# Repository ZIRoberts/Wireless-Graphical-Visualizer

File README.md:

# Wireless-Graphical-Visualizer
Maintain all documents relating to the creation of the Realtime Wireless Graphical Equalizer.  All symbols, schematics, footprints, and board layouts are designed in KiCad.

# Overview

There is a single board in this sytem and it is broken up into three sections represented by their own respeitive schematic sheet. The first section is the board's inputs. This includes the audio input, power input and regulation, and the audio isolation buffer. Audio is input by a standard 3.5 mm audio cable through one of the two linked audio jacks and enters the system by passing through the unity gain isolation buffer. The two audio jacks are to allow for the user to pass the audio through the device to a speaker without any disortion caused by the filters. Power is inputed by a standard USB Type-B mini cable. There are two 2.5 V linear regulators connected directly to the input line. One serves as a virtual ground to refence the audio signal two later in on in the single supply band pass filters. The other is used on the output of the filters as a voltage calmp to ensure the microcontroller will not get damaged due to an unexpectedly large singal being passed through the filters.

The second section is the bandpass filter section. There are 8 multiple feedback band pass filters. Multifple feed back band pass fitlers were selected based on their low componet cost, moderate gain, and able to handle to filter a signal up to around 5 Q. The 8 bands are tuned to the fallowing frequnecies: 160, 250, 400, 800, 1000, 2500, 4000, and 6500 Hz. The frequncies are filted through their specified filter, have their DC offset stripped, pass through a half-wave rectifer and a 22 uF capacitor to keep the signal from instantly dissapating. This output is then passed through a voltage clamp consiting of a 2.5 V linear regulator and a 500 mV foward voltage diode to prevent the output signal from passive above 3 V as any input above 3V3 would fry the microcontroller. 

The third section is the microcontoller and multiplexor. This section cotnains the connections for the selected ESP32 microcontroller along with the mux. The mux is used to select which of the 8 filtered outputs would be read in by the microcontroller. The MCU used for this project is the ESP32 by Espressiff Systems. This microcontroller was sekected because it was of appropriate size, had appropriate pin count, built in wireless communication, compatablity with Arduino libraries, and the creator already had experience using this family of microcontrollers. This sheet also holds the diodes used for the voltage clamp discribed on in the previous section.

A full list of electronic components can be found in the Bill of Materials.xlsx and images of the design can be found below.

# Schematic
## Aduio and Power Sheet

## Bandpass Filter Sheet

## Microcontroller sheet

# PCB Layout
## Front Copper 

## Back Copper

# 3D Renders
## Front Render

## Bottom Render

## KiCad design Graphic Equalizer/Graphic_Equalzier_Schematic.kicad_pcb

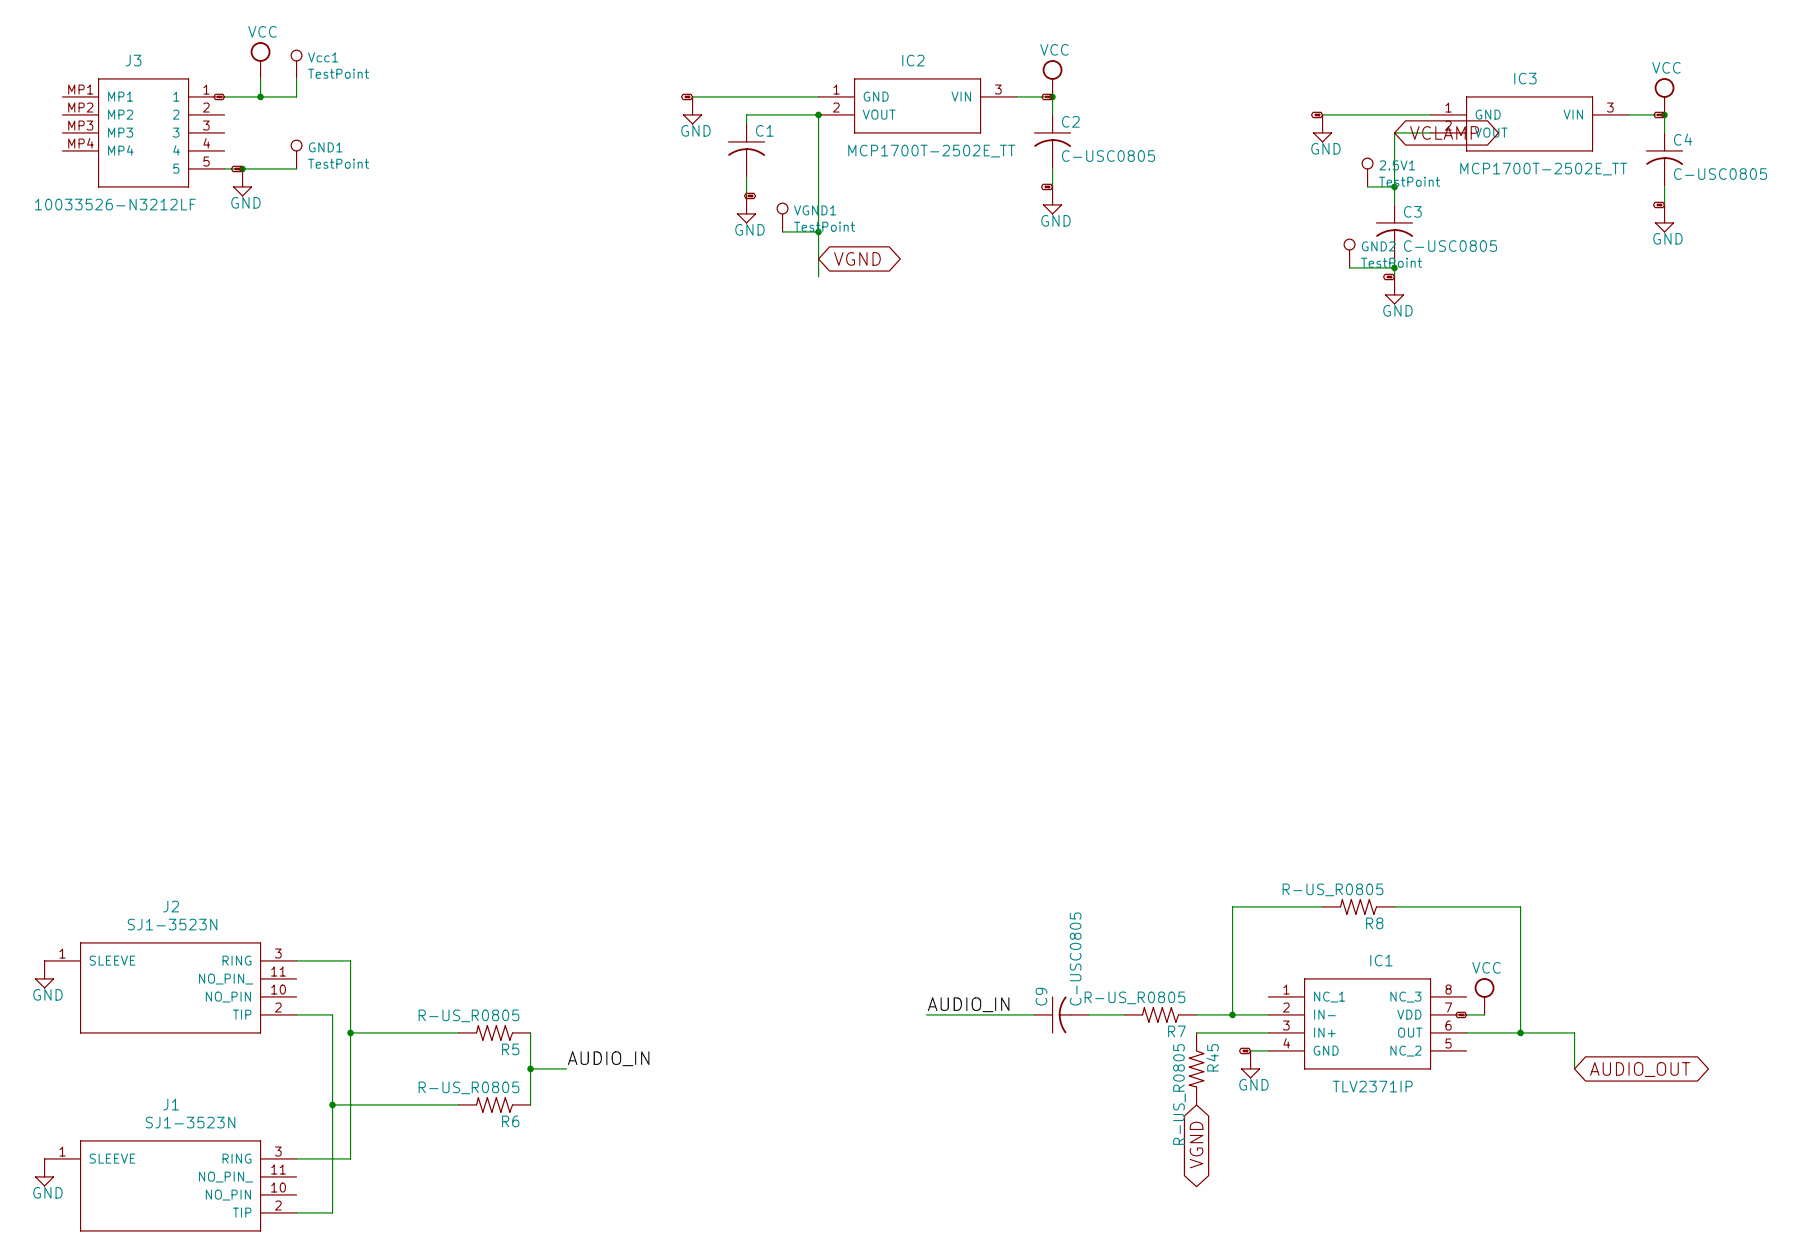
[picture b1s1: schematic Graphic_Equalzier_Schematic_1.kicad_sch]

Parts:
2.5V1: TestPoint; TestPoint_THTPad_D2.0mm_Drill1.0mm
C1, C2, C3, C4, C9: C-USC0805; C0805
GND1, GND2: TestPoint; TestPoint_THTPad_D2.0mm_Drill1.0mm
IC1: TLV2371IP; DIP794W53P254L959H508Q8N
IC2, IC3: MCP1700T-2502E_TT; SOT95P237X112-3N
J1, J2: SJ1-3523N; SJ13523N
J3: 10033526-N3212LF; 10033526N3212LF
R5, R6, R7, R8, R45: R-US_R0805; R0805
VGND1: TestPoint; TestPoint_THTPad_D2.0mm_Drill1.0mm
Vcc1: TestPoint; TestPoint_THTPad_D2.0mm_Drill1.0mm

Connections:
/Graphic_Equalzier_Schematic_1/AUDIO_IN: C9.1, R5.1, R6.1
AUDIO_OUT: IC1.6 (OUT), R8.1; also elsewhere on the board
GND: C1.2, C2.2, C3.2, C4.2, GND1.1, GND2.1, IC1.4 (GND), IC2.1 (GND), IC3.1 (GND), J1.1 (SLEEVE), J2.1 (SLEEVE), J3.5; also elsewhere on the board
unnamed: C9.2, R7.2
unnamed: IC1.2 (IN-), R7.1, R8.2
unnamed: IC1.3 (IN+), R45.1
unnamed: J1.2 (TIP), J2.2 (TIP), R6.2
unnamed: J1.3 (RING), J2.3 (RING), R5.2
VCC: C2.1, C4.1, IC1.7 (VDD), IC2.3 (VIN), IC3.3 (VIN), J3.1, Vcc1.1; also elsewhere on the board
VCLAMP: 2.5V1.1, C3.1, IC3.2 (VOUT); also elsewhere on the board
VGND: C1.1, IC2.2 (VOUT), R45.2, VGND1.1; also elsewhere on the board

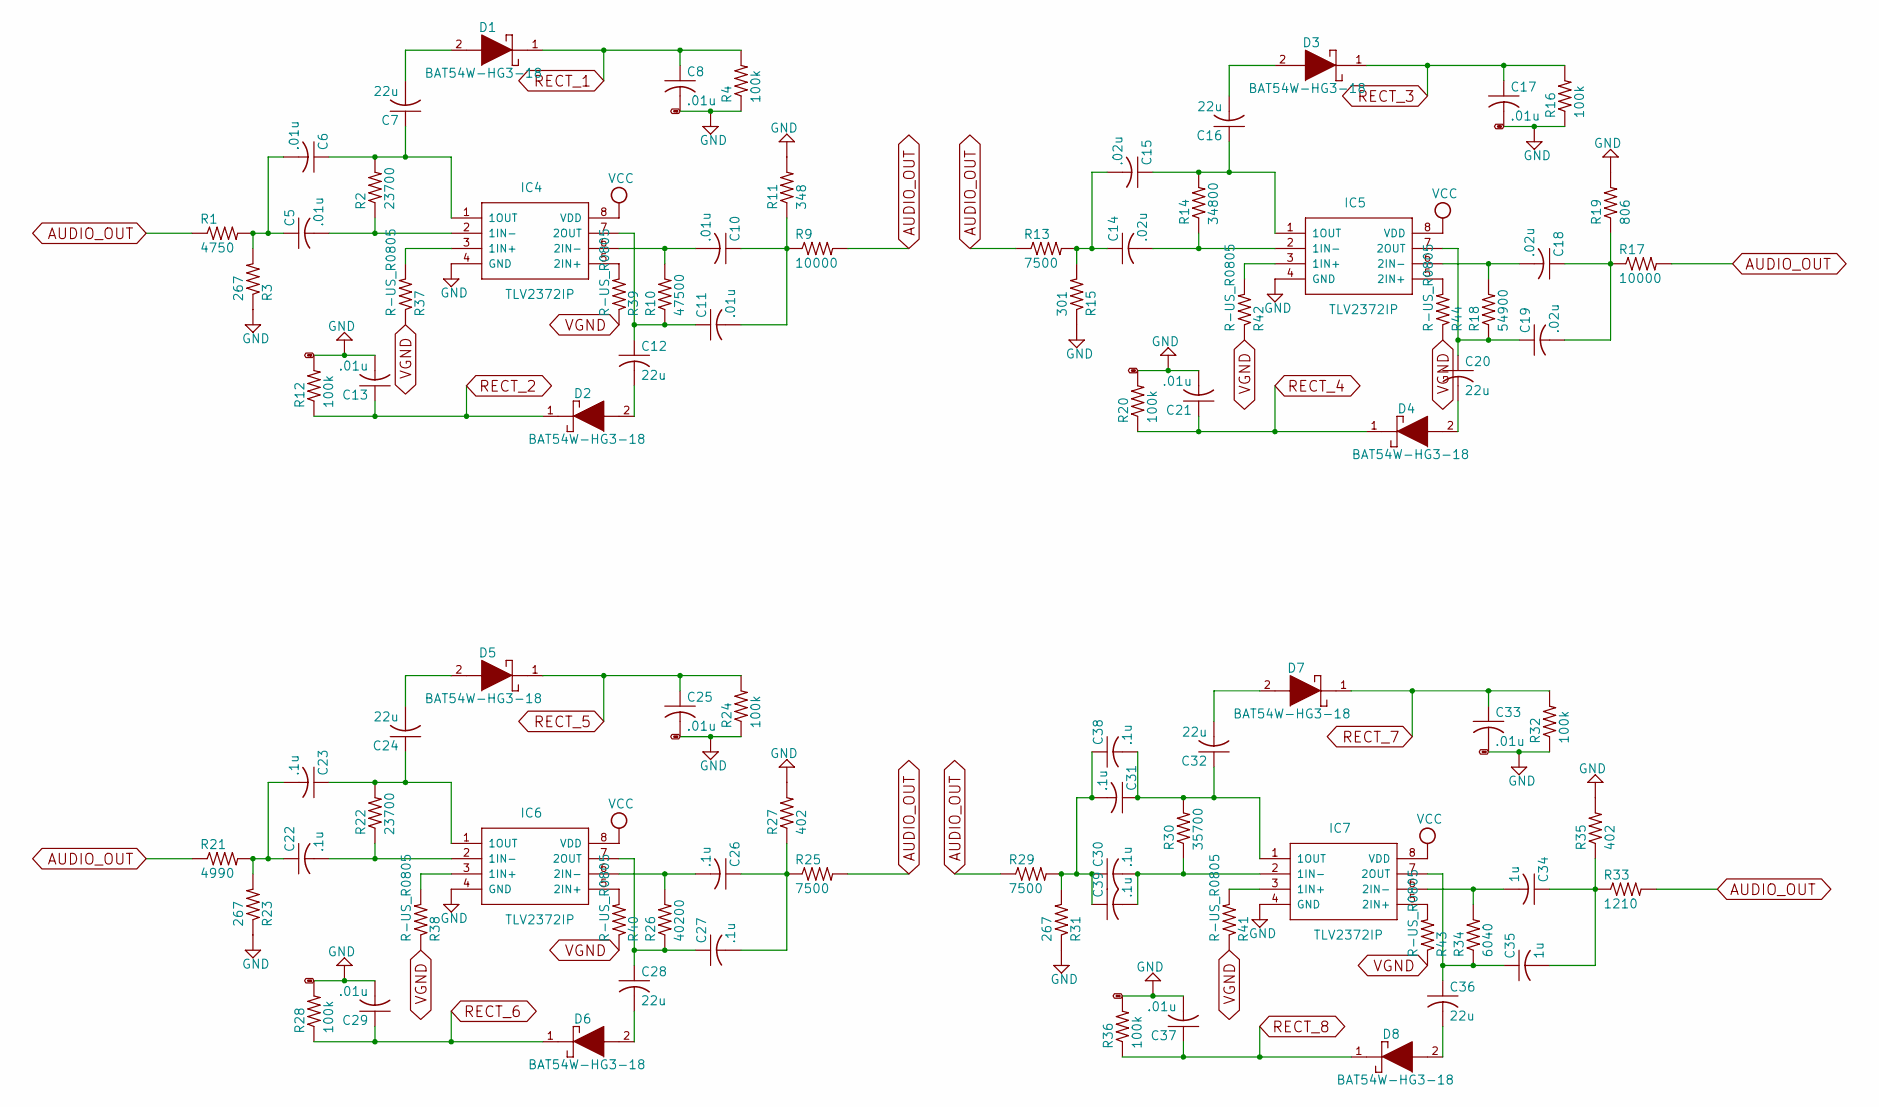
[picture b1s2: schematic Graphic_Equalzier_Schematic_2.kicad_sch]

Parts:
C5, C6, C8, C10, C11, C13, C17, C21, C25, C29, C33, C37: .01u; C0805
C7, C12, C16, C20, C24, C28, C32, C36: 22u; C0805
C14, C15, C18, C19: .02u; C0805
C22, C23, C26, C27, C30, C31, C38, C39: .1u; C0805
C34, C35: 1u; C0805
D1, D2, D3, D4, D5, D6, D7, D8: BAT54W-HG3-18; SOD3716X135N
IC4, IC5, IC6, IC7: TLV2372IP; DIP794W53P254L959H508Q8N
R1: 4750; R0805
R2, R22: 23700; R0805
R3, R23, R31: 267; R0805
R4, R12, R16, R20, R24, R28, R32, R36: 100k; R0805
R9, R17: 10000; R0805
R10: 47500; R0805
R11: 348; R0805
R13: 7500; R_0805_2012Metric_Pad1.20x1.40mm_HandSolder
R14: 34800; R0805
R15: 301; R0805
R18: 54900; R0805
R19: 806; R0805
R21: 4990; R0805
R25, R29: 7500; R0805
R26: 40200; R0805
R27, R35: 402; R0805
R30: 35700; R0805
R33: 1210; R0805
R34: 6040; R0805
R37, R38, R39, R40, R41, R42, R43, R44: R-US_R0805; R0805

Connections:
AUDIO_OUT: R1.1, R9.2, R13.1, R17.2, R21.1, R25.2, R29.1, R33.2; also elsewhere on the board
GND: C8.2, C13.2, C17.2, C21.2, C25.2, C29.2, C33.2, C37.2, IC4.4 (GND), IC5.4 (GND), IC6.4 (GND), IC7.4 (GND), R3.1, R4.1, R11.2, R12.2, R15.1, R16.1, R19.2, R20.2, R23.1, R24.1, R27.2, R28.2, R31.1, R32.1, R35.2, R36.2; also elsewhere on the board
unnamed: C5.1, C6.2, R1.2, R3.2
unnamed: C5.2, IC4.2 (1IN-), R2.1
unnamed: C6.1, C7.1, IC4.1 (1OUT), R2.2
unnamed: C7.2, D1.2 (A)
unnamed: C10.1, C11.2, R9.1, R11.1
unnamed: C10.2, IC4.6 (2IN-), R10.2
unnamed: C11.1, C12.1, IC4.7 (2OUT), R10.1
unnamed: C12.2, D2.2 (A)
unnamed: C14.1, C15.2, R13.2, R15.2
unnamed: C14.2, IC5.2 (1IN-), R14.1
unnamed: C15.1, C16.1, IC5.1 (1OUT), R14.2
unnamed: C16.2, D3.2 (A)
unnamed: C18.1, C19.2, R17.1, R19.1
unnamed: C18.2, IC5.6 (2IN-), R18.2
unnamed: C19.1, C20.1, IC5.7 (2OUT), R18.1
unnamed: C20.2, D4.2 (A)
unnamed: C22.1, C23.2, R21.2, R23.2
unnamed: C22.2, IC6.2 (1IN-), R22.1
unnamed: C23.1, C24.1, IC6.1 (1OUT), R22.2
unnamed: C24.2, D5.2 (A)
unnamed: C26.1, C27.2, R25.1, R27.1
unnamed: C26.2, IC6.6 (2IN-), R26.2
unnamed: C27.1, C28.1, IC6.7 (2OUT), R26.1
unnamed: C28.2, D6.2 (A)
unnamed: C30.1, C31.2, C38.1, C39.1, R29.2, R31.2
unnamed: C30.2, C39.2, IC7.2 (1IN-), R30.1
unnamed: C31.1, C32.1, C38.2, IC7.1 (1OUT), R30.2
unnamed: C32.2, D7.2 (A)
unnamed: C34.1, C35.2, R33.1, R35.1
unnamed: C34.2, IC7.6 (2IN-), R34.2
unnamed: C35.1, C36.1, IC7.7 (2OUT), R34.1
unnamed: C36.2, D8.2 (A)
unnamed: IC4.3 (1IN+), R37.2
unnamed: IC4.5 (2IN+), R39.2
unnamed: IC5.3 (1IN+), R42.2
unnamed: IC5.5 (2IN+), R44.2
unnamed: IC6.3 (1IN+), R38.2
unnamed: IC6.5 (2IN+), R40.2
unnamed: IC7.3 (1IN+), R41.2
unnamed: IC7.5 (2IN+), R43.2
RECT_1: C8.1, D1.1 (K), R4.2; also elsewhere on the board
RECT_2: C13.1, D2.1 (K), R12.1; also elsewhere on the board
RECT_3: C17.1, D3.1 (K), R16.2; also elsewhere on the board
RECT_4: C21.1, D4.1 (K), R20.1; also elsewhere on the board
RECT_5: C25.1, D5.1 (K), R24.2; also elsewhere on the board
RECT_6: C29.1, D6.1 (K), R28.1; also elsewhere on the board
RECT_7: C33.1, D7.1 (K), R32.2; also elsewhere on the board
RECT_8: C37.1, D8.1 (K), R36.1; also elsewhere on the board
VCC: IC4.8 (VDD), IC5.8 (VDD), IC6.8 (VDD), IC7.8 (VDD); also elsewhere on the board
VGND: R37.1, R38.1, R39.1, R40.1, R41.1, R42.1, R43.1, R44.1; also elsewhere on the board

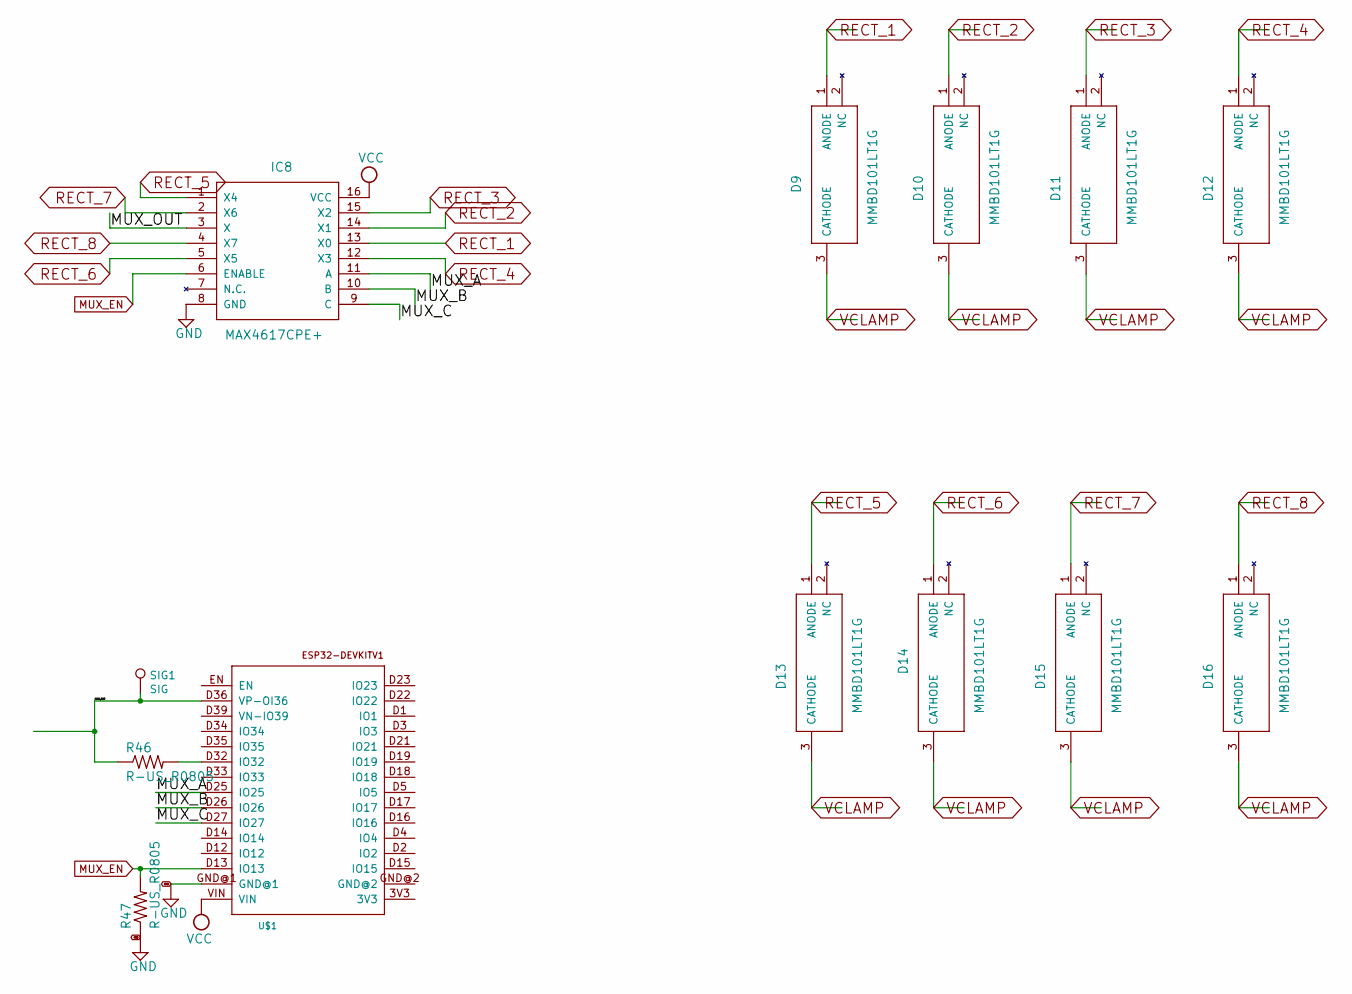
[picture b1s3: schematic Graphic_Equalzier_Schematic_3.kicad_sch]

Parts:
D9, D10, D11, D12, D13, D14, D15, D16: MMBD101LT1G; SOT96P237X111-3N
IC8: MAX4617CPE+; DIP794W56P254L1918H457Q16N
R46, R47: R-US_R0805; R0805
SIG1: SIG; TestPoint_THTPad_D2.0mm_Drill1.0mm
U$1: ESP32DEVKITV1; ESP32-DEVKITV1

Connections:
/Graphic_Equalzier_Schematic_3/MUX_A: IC8.11 (A), U$1.D25 (IO25)
/Graphic_Equalzier_Schematic_3/MUX_B: IC8.10 (B), U$1.D26 (IO26)
/Graphic_Equalzier_Schematic_3/MUX_C: IC8.9 (C), U$1.D27 (IO27)
/Graphic_Equalzier_Schematic_3/MUX_OUT: IC8.3 (X), R46.1, SIG1.1, U$1.D36 (VP-OI36); also elsewhere on the board
GND: IC8.8 (GND), R47.1, U$1.GND@1; also elsewhere on the board
MUX_EN: IC8.6 (ENABLE), R47.2, U$1.D13 (IO13)
unnamed: R46.2, U$1.D32 (IO32)
RECT_1: D9.1 (ANODE), IC8.13 (X0); also elsewhere on the board
RECT_2: D10.1 (ANODE), IC8.14 (X1); also elsewhere on the board
RECT_3: D11.1 (ANODE), IC8.15 (X2); also elsewhere on the board
RECT_4: D12.1 (ANODE), IC8.12 (X3); also elsewhere on the board
RECT_5: D13.1 (ANODE), IC8.1 (X4); also elsewhere on the board
RECT_6: D14.1 (ANODE), IC8.5 (X5); also elsewhere on the board
RECT_7: D15.1 (ANODE), IC8.2 (X6); also elsewhere on the board
RECT_8: D16.1 (ANODE), IC8.4 (X7); also elsewhere on the board
VCC: IC8.16 (VCC), U$1.VIN; also elsewhere on the board
VCLAMP: D9.3 (CATHODE), D10.3 (CATHODE), D11.3 (CATHODE), D12.3 (CATHODE), D13.3 (CATHODE), D14.3 (CATHODE), D15.3 (CATHODE), D16.3 (CATHODE); also elsewhere on the board

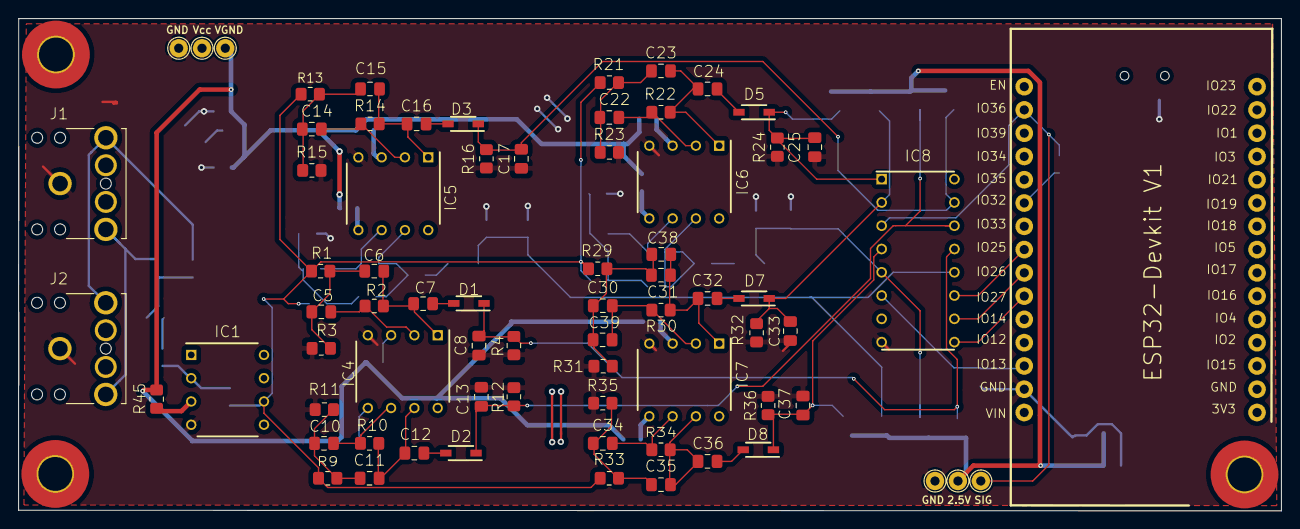
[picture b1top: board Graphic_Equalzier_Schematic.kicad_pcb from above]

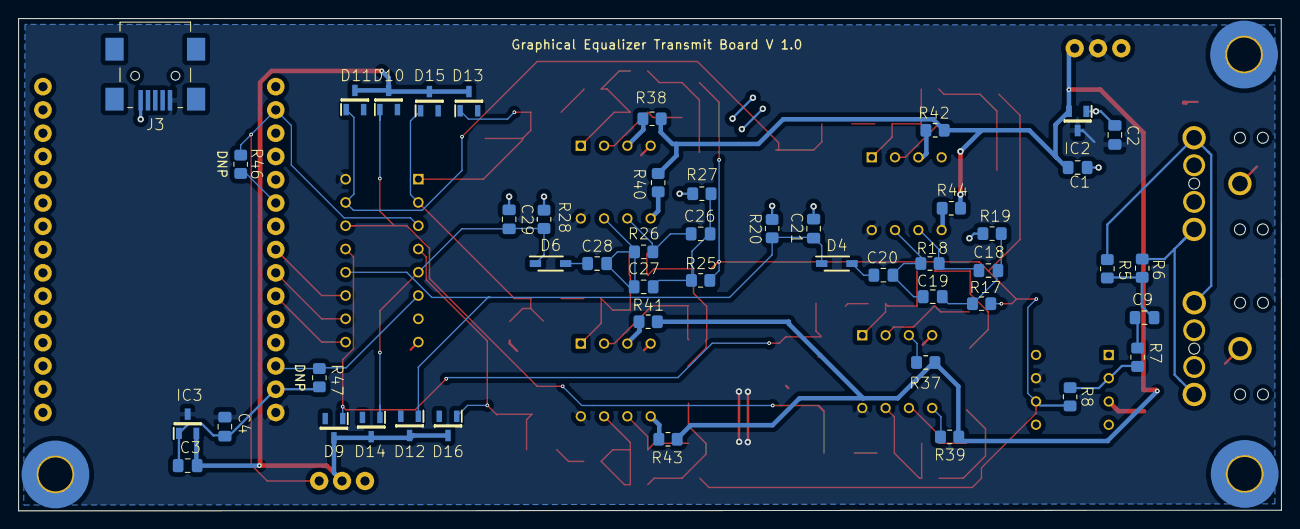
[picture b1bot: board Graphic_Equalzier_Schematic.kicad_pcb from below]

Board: 2 copper layers, 137.8 x 53.7 mm, 123 parts (48 on the bottom side), 65 nets.

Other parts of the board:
2.5V: TestPoint; TestPoint_THTPad_D2.0mm_Drill1.0mm
 : MountingHole_3.7mm_Pad_TopBottom
 #2,  #3: MountingHole_3.7mm_Pad_TopBottom
GND: TestPoint; TestPoint_THTPad_D2.0mm_Drill1.0mm
GND#2: TestPoint; TestPoint_THTPad_D2.0mm_Drill1.0mm
SIG: SIG; TestPoint_THTPad_D2.0mm_Drill1.0mm
VGND: TestPoint; TestPoint_THTPad_D2.0mm_Drill1.0mm
Vcc: TestPoint; TestPoint_THTPad_D2.0mm_Drill1.0mm

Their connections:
/Graphic_Equalzier_Schematic_3/MUX_OUT: SIG.1; also elsewhere on the board
GND: GND.1, GND#2.1; also elsewhere on the board
VCC: Vcc.1; also elsewhere on the board
VCLAMP: 2.5V.1; also elsewhere on the board
VGND: VGND.1; also elsewhere on the board

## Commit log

2022-12-04 Update README.md
    renamed repository
2022-12-04 Initial commit
    Added KiCad Project, BOM, and Single stage Bandpass filter simulator
